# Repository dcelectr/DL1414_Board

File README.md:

# DL1414_Board
Board design files for Litronix / Siemens / HP DL1414 16-Segment LED displays.
Each board can be stacked with another board and increase the number on total digits.

Arduino test code (scrolling text) for one module is in the [DL1414_74HC595](https://github.com/dcelectr/DL1414_Board/blob/main/DL1414_74HC595/DL1414_74HC595.ino) folder.

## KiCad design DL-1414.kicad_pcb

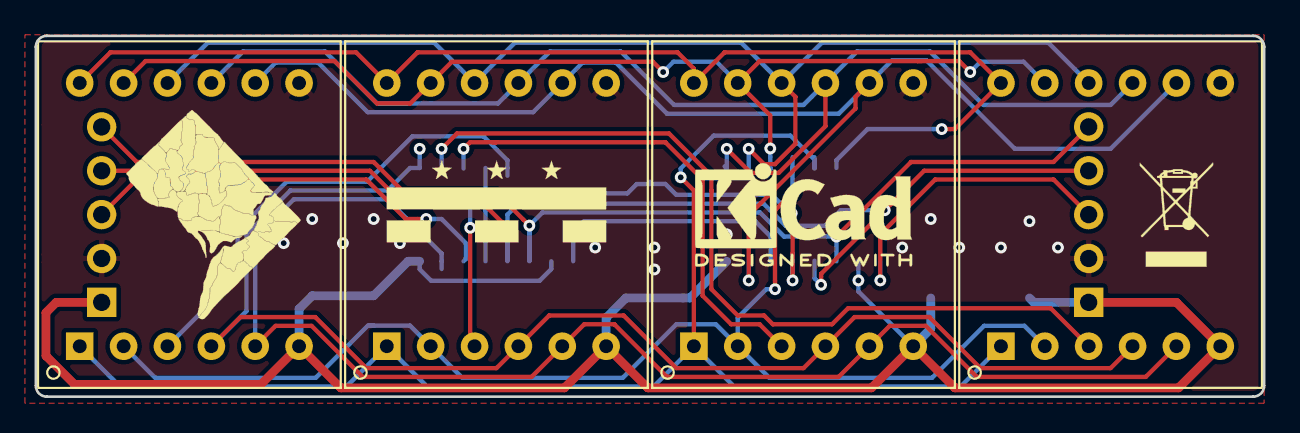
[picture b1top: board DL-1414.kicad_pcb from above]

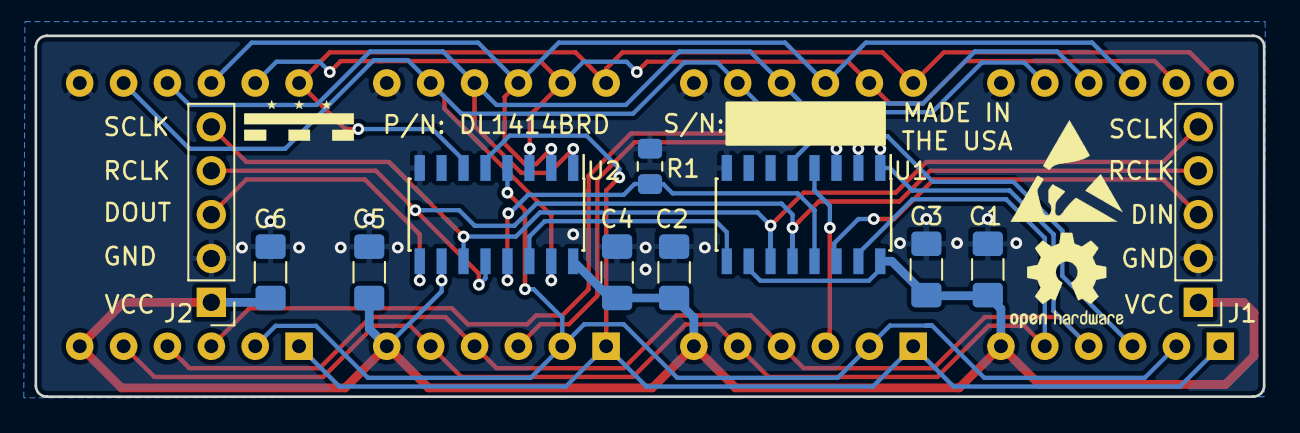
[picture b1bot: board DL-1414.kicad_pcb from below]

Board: 2 copper layers, 71.1 x 20.9 mm, 15 parts (11 on the bottom side), 21 nets.

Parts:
C1, C2, C3, C4, C5, C6: C; C_1206_3216Metric_Pad1.42x1.75mm_HandSolder
J1, J2: Conn_01x05_Male; PinHeader_1x05_P2.54mm_Vertical
R1: R; R_0805_2012Metric_Pad1.15x1.40mm_HandSolder
U1, U2: 74HC595; SOIC-16_3.9x9.9mm_P1.27mm
U3, U4, U5, U6: DL1414

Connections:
+5V: C1.1, C2.1, C3.1, C4.1, C5.1, C6.1, J1.1, J2.1, U1.10, U1.16, U2.10, U2.16, U3.6, U4.6, U5.6, U6.6
/A0: U1.15, U3.5, U4.5, U5.5, U6.5
/A1: U1.1, U3.4, U4.4, U5.4, U6.4
/D0: U2.15, U3.8, U4.8, U5.8, U6.8
/D1: U2.1, U3.9, U4.9, U5.9, U6.9
/D2: U2.2, U3.10, U4.10, U5.10, U6.10
/D3: U2.3, U3.11, U4.11, U5.11, U6.11
/D4: U2.4, U3.2, U4.2, U5.2, U6.2
/D5: U2.5, U3.1, U4.1, U5.1, U6.1
/D6: U2.6, U3.12, U4.12, U5.12, U6.12
/DIN: J1.3, U1.14
/DOUT: J2.3, U2.9
/RCLK: J1.4, J2.4, U1.12, U2.12
/SER: U1.9, U2.14
/SRCLK: J1.5, J2.5, U1.11, U2.11
/nOE: R1.1, U1.13, U2.13
/nWR0: U1.2, U6.3
/nWR1: U1.3, U5.3
/nWR2: U1.4, U4.3
/nWR3: U1.5, U3.3
GND: C1.2, C2.2, C3.2, C4.2, C5.2, C6.2, J1.2, J2.2, R1.2, U1.8, U2.8, U3.7, U4.7, U5.7, U6.7

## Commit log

2021-08-17 Add files via upload
    Initial Commit
